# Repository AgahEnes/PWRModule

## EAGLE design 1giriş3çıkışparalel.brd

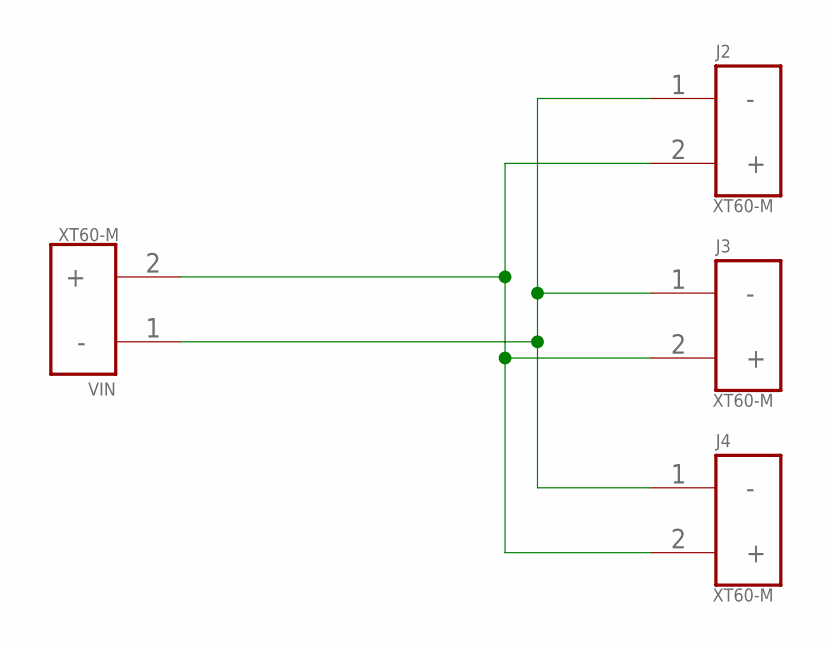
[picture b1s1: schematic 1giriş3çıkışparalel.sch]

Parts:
J2, J3, J4: XT60-M; AMASS_XT60-M
VIN: XT60-M; AMASS_XT60-M

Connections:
unnamed: J2.1 (-), J3.1 (-), J4.1 (-), VIN.1 (-)
unnamed: J2.2 (+), J3.2 (+), J4.2 (+), VIN.2 (+)

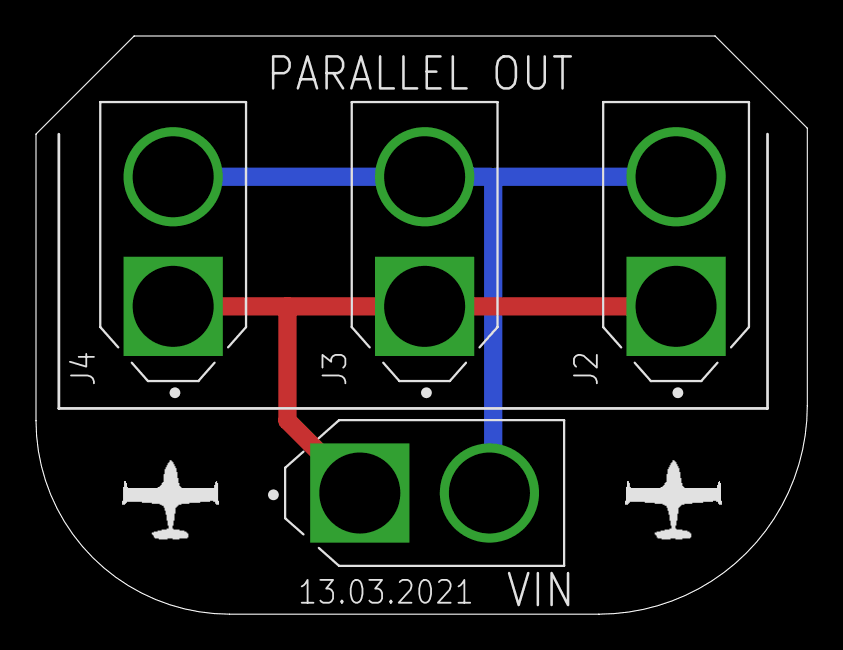
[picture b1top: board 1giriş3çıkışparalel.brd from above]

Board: 2 copper layers, 42.9 x 32.1 mm, 4 parts (0 on the bottom side), 2 nets.

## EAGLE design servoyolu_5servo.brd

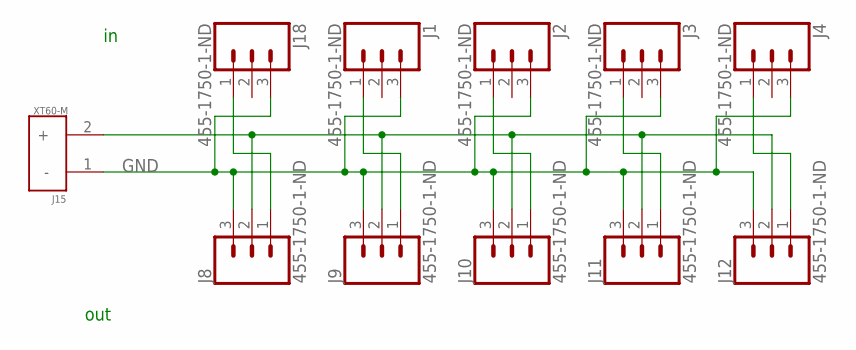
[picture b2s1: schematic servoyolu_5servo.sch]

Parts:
J1, J2, J3, J4, J8, J9, J10, J11, J12, J18: 455-1750-1-ND; 1X03
J15: XT60-M; AMASS_XT60-M

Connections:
GND: J1.3, J2.3, J3.3, J4.3, J8.3, J9.3, J10.3, J11.3, J12.3, J15.1 (-), J18.3
unnamed: J8.1, J18.1
unnamed: J1.1, J9.1
unnamed: J2.1, J10.1
unnamed: J3.1, J11.1
unnamed: J4.1, J12.1
unnamed: J8.2, J9.2, J10.2, J11.2, J12.2, J15.2 (+)

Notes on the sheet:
out

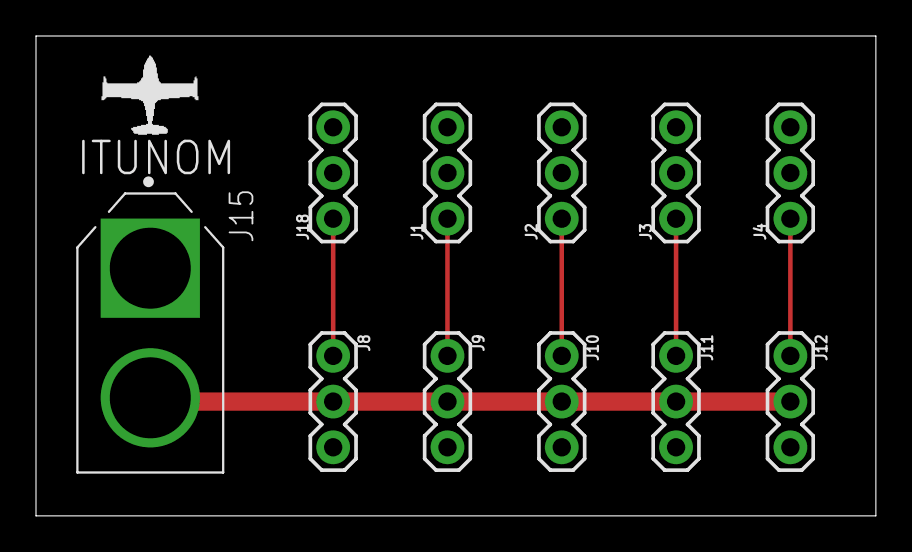
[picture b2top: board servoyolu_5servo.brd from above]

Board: 2 copper layers, 46.7 x 26.7 mm, 11 parts (0 on the bottom side), 7 nets.

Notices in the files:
parts and their libraries:
SparkFun-Connectors: Licensing: Creative Commons ShareAlike 4.0 International - https://creativecommons.org/licenses/by-sa/4.0
